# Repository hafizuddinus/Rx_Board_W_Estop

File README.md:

kicanvas layout and schematic:
- schematic : https://kicanvas.org/?repo=https%3A%2F%2Fgithub.com%2Fhafizuddinus%2FRx_Board_W_Estop%2Fblob%2Fmain%2FnRF24L01.kicad_sch
- layout : https://kicanvas.org/?repo=https%3A%2F%2Fgithub.com%2Fhafizuddinus%2FRx_Board_W_Estop%2Fblob%2Fmain%2FnRF24L01.kicad_pcb

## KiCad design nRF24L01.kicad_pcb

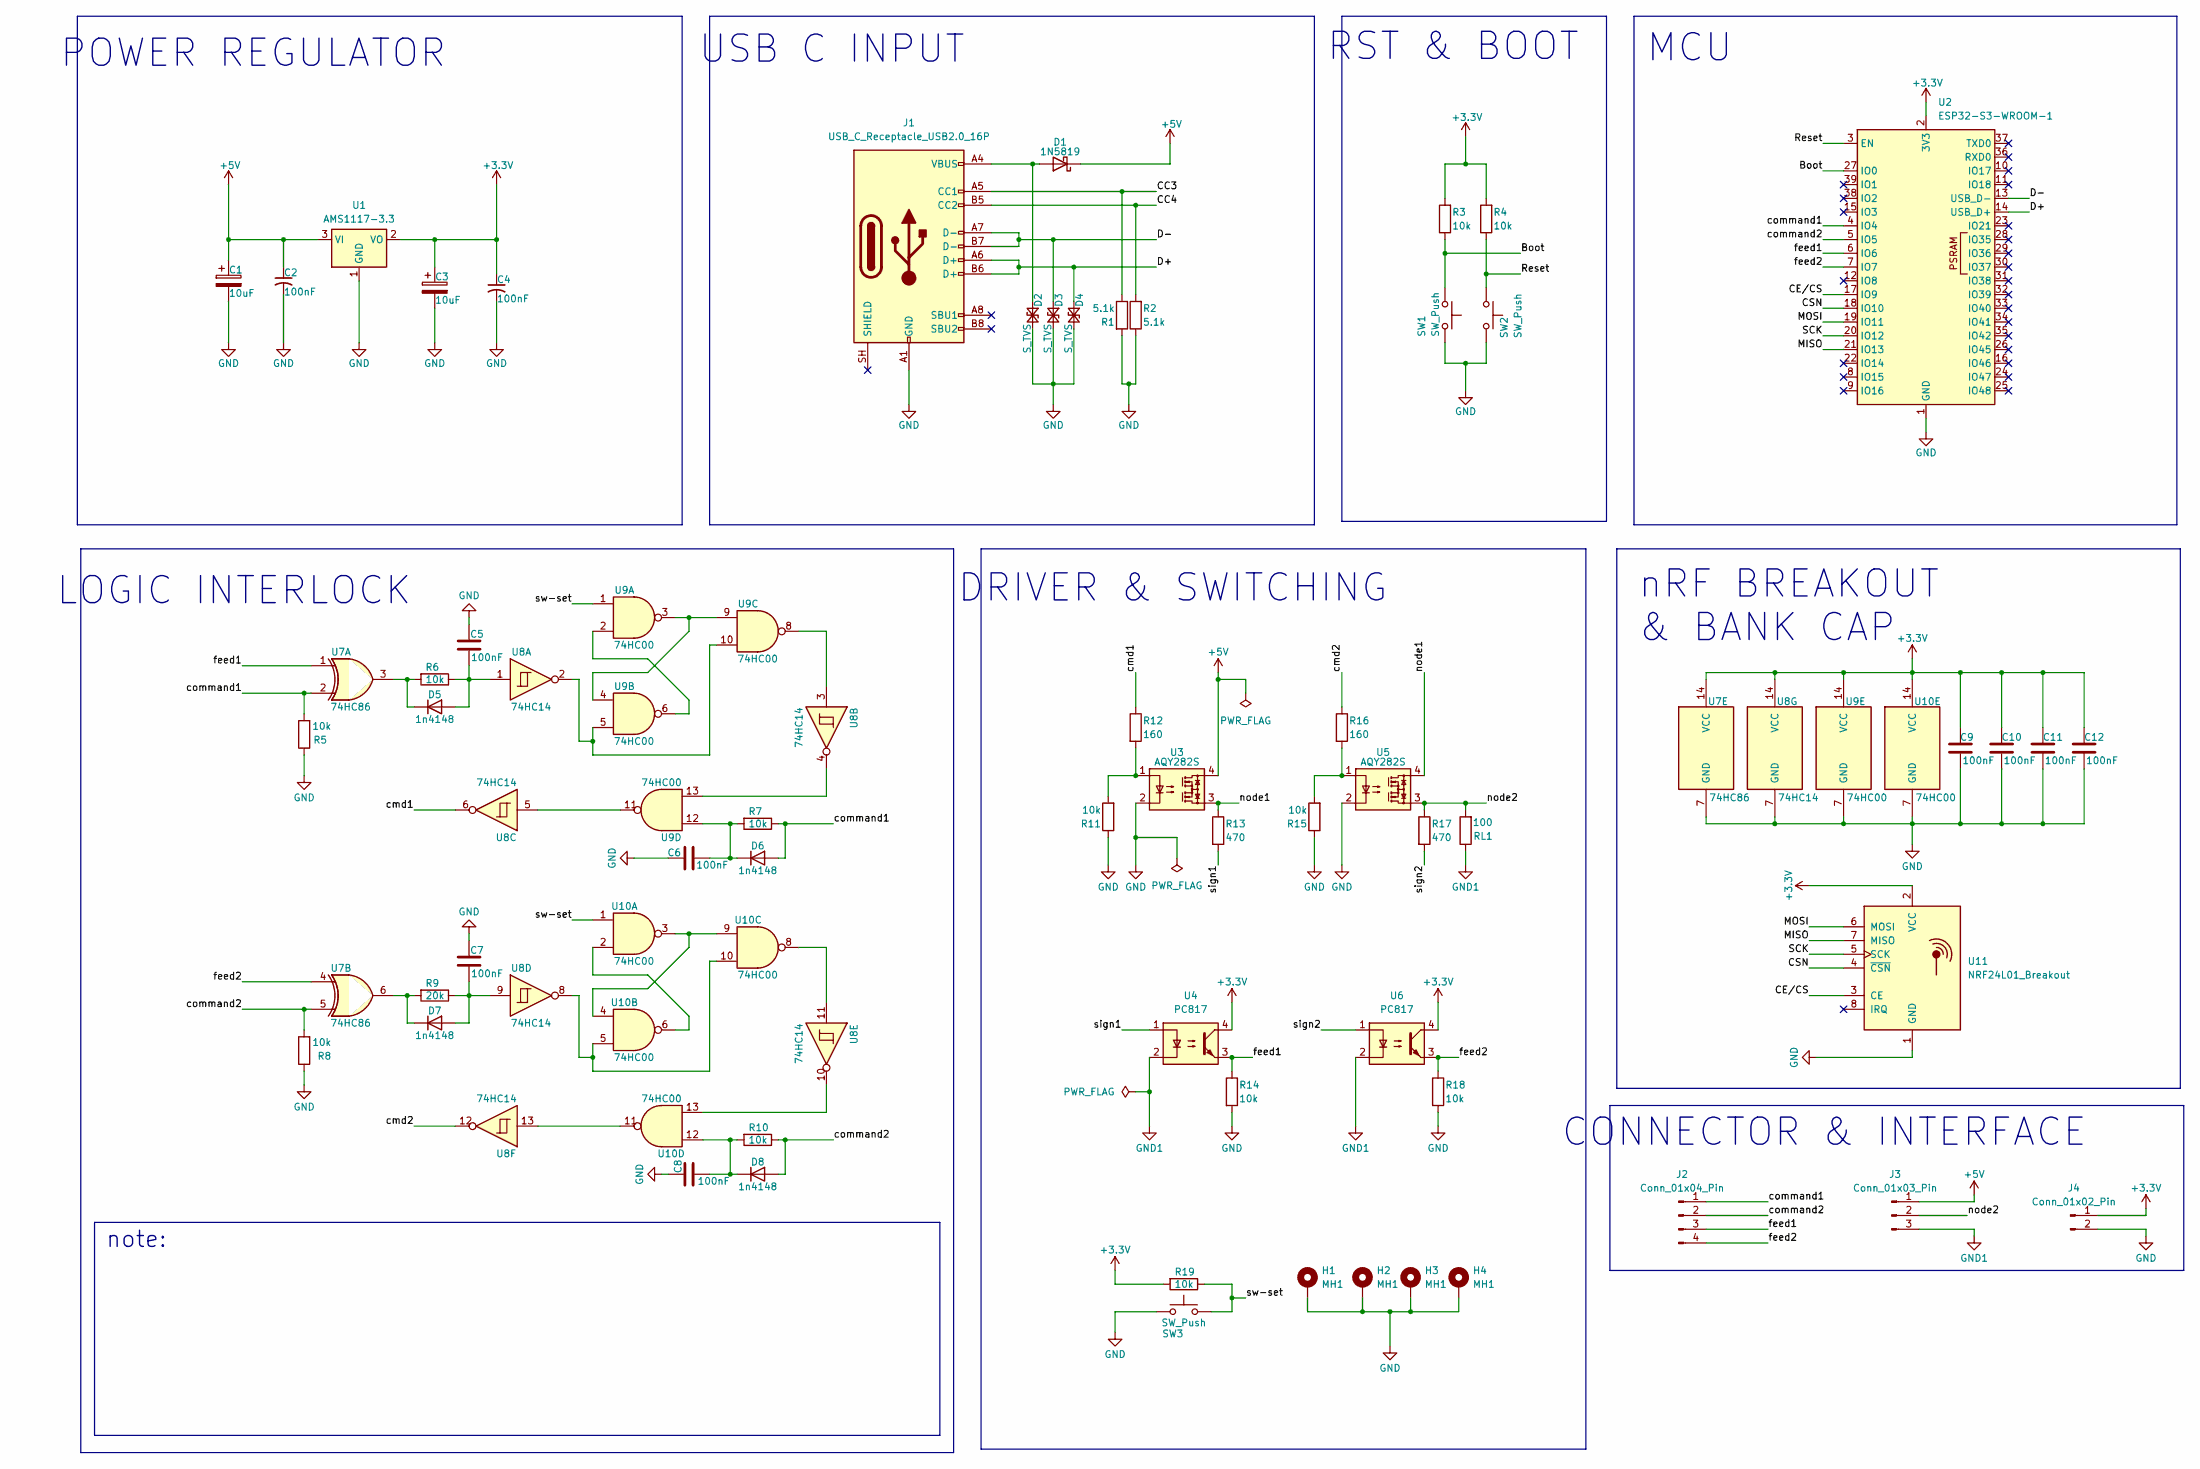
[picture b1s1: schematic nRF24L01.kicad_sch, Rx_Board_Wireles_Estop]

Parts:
C1, C3: 10uF; C_0603_1608Metric
C2, C4, C5, C6, C7, C8, C9, C10, C11, C12: 100nF; C_0603_1608Metric
D1: 1N5819; D_SOD-123
D2, D3, D4: S_TVS; D_SOD-323
D5, D6, D7, D8: 1n4148; D_0603_1608Metric
H1, H2, H3, H4: MH1; MountingHole_3.2mm_M3_Pad
J1: USB_C_Receptacle_USB2.0_16P; USB_C_Receptacle_HRO_TYPE-C-31-M-12
J2: Conn_01x04_Pin; JST_EH_B4B-EH-A_1x04_P2.50mm_Vertical
J3: Conn_01x03_Pin; TerminalBlock_Phoenix_MKDS-1,5-3-5.08_1x03_P5.08mm_Horizont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
J4: Conn_01x02_Pin; JST_EH_S2B-EH_1x02_P2.50mm_Horizontal
R1, R2: 5.1k; R_0805_2012Metric
R3, R4: 10k; R_0805_2012Metric
R5, R6, R7, R8, R10, R11, R14, R15, R18, R19: 10k; R_0603_1608Metric
R9: 20k; R_0603_1608Metric
R12, R16: 160; R_0603_1608Metric
R13, R17: 470; R_0603_1608Metric
RL1: 100; R_0603_1608Metric
SW1, SW2: SW_Push; SW_Push_SPST_NO_Alps_SKRK
SW3: SW_Push; SW_Push_1P1T_NO_CK_KMR2
U1: AMS1117-3.3; SOT-223-3_TabPin2
U2: ESP32-S3-WROOM-1
U3, U5: AQY282S; SO-4_4.4x4.3mm_P2.54mm
U4, U6: PC817; DIP-4_W7.62mm
U7: 74HC86; DIP-14_W7.62mm
U8: 74HC14; DIP-14_W7.62mm
U9, U10: 74HC00; SOIC-14_3.9x8.7mm_P1.27mm
U11: NRF24L01_Breakout; nRF24L01_Breakout

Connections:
+3.3V: C3.1, C4.1, C9.2, C10.2, C11.2, C12.2, J4.1, R3.2, R4.2, R19.2, U1.2 (VO), U2.2 (3V3), U4.4, U6.4, U7.14 (VCC), U8.14 (VCC), U9.14 (VCC), U10.14 (VCC), U11.2 (VCC)
+5V: C1.1, C2.1, D1.1 (K), J3.1, U1.3 (VI), U3.4
/Boot: R3.1, SW1.1, U2.27 (IO0)
/CC3: J1.A5 (CC1), R1.1
/CC4: J1.B5 (CC2), R2.2
/CE/CS: U2.17 (IO9), U11.3 (CE)
/CSN: U2.18 (IO10), U11.4 (~CSN)
/D+: D4.1 (A1), J1.A6 (D+), J1.B6 (D+), U2.14 (USB_D+)
/D-: D3.1 (A1), J1.A7 (D-), J1.B7 (D-), U2.13 (USB_D-)
/MISO: U2.21 (IO13), U11.7 (MISO)
/MOSI: U2.19 (IO11), U11.6 (MOSI)
/Reset: R4.1, SW2.1, U2.3 (EN)
/SCK: U2.20 (IO12), U11.5 (SCK)
/cmd1: R12.1, U8.6
/cmd2: R16.1, U8.12
/command1: D6.2 (A), J2.1, R5.2, R7.1, U2.4 (IO4), U7.2
/command2: D8.2 (A), J2.2, R8.2, R10.1, U2.5 (IO5), U7.5
/feed1: J2.3, R14.1, U2.6 (IO6), U4.3, U7.1
/feed2: J2.4, R18.1, U2.7 (IO7), U6.3, U7.4
/node1: R13.1, U3.3, U5.4
/node2: J3.2, R17.1, RL1.2, U5.3
/sign1: R13.2, U4.1
/sign2: R17.2, U6.1
/sw-set: R19.1, SW3.2, U9.1, U10.1
GND: C1.2, C2.2, C3.2, C4.2, C5.2, C6.2, C7.2, C8.2, C9.1, C10.1, C11.1, C12.1, D2.2 (A2), D3.2 (A2), D4.2 (A2), H1.1, H2.1, H3.1, H4.1, J1.A1 (GND), J1.A12 (GND), J1.B1 (GND), J1.B12 (GND), J4.2, R1.2, R2.1, R5.1, R8.1, R11.1, R14.2, R15.1, R18.2, SW1.2, SW2.2, SW3.1, U1.1 (GND), U2.1 (GND), U2.40 (GND), U2.41 (GND), U3.2, U5.2, U7.7 (GND), U8.7 (GND), U9.7 (GND), U10.7 (GND), U11.1 (GND)
GND1: J3.3, RL1.1, U4.2, U6.2
unnamed: D1.2 (A), D2.1 (A1), J1.A4 (VBUS), J1.A9 (VBUS), J1.B4 (VBUS), J1.B9 (VBUS)
unnamed: C5.1, D5.2 (A), R6.1, U8.1
unnamed: D5.1 (K), R6.2, U7.3
unnamed: C6.1, D6.1 (K), R7.2, U9.12
unnamed: C7.1, D7.2 (A), R9.1, U8.9
unnamed: D7.1 (K), R9.2, U7.6
unnamed: C8.1, D8.1 (K), R10.2, U10.12
unnamed: R11.2, R12.2, U3.1
unnamed: R15.2, R16.2, U5.1
unnamed: U8.2, U9.5, U9.10
unnamed: U8.3, U9.8
unnamed: U8.4, U9.13
unnamed: U8.5, U9.11
unnamed: U9.2, U9.6
unnamed: U9.3, U9.4, U9.9
unnamed: U10.2, U10.6
unnamed: U10.3, U10.4, U10.9
unnamed: U8.11, U10.8
unnamed: U8.8, U10.5, U10.10
unnamed: U8.13, U10.11
unnamed: U8.10, U10.13

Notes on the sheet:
MCU
RST & BOOT
LOGIC INTERLOCK
nRF BREAKOUT & BANK CAP
CONNECTOR & INTERFACE
note:
DRIVER & SWITCHING
POWER REGULATOR
USB C INPUT

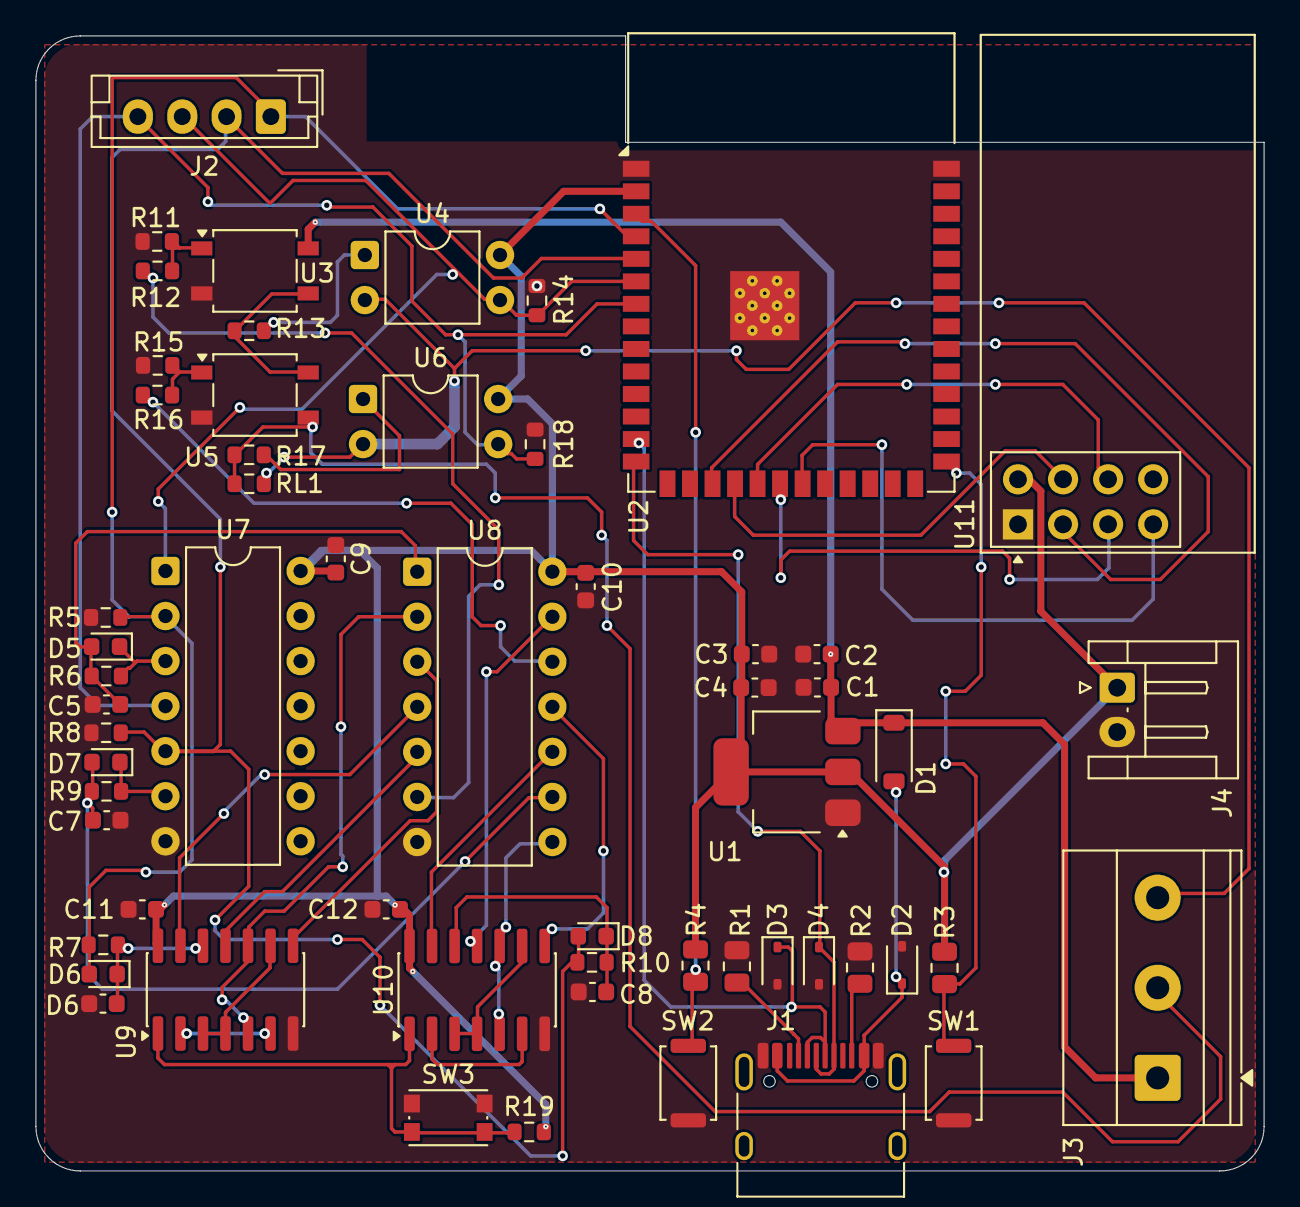
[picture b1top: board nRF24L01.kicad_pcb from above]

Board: 2 copper layers, 69.2 x 64.0 mm, 58 parts (0 on the bottom side), 47 nets.
